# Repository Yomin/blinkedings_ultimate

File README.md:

# Blinkedings Ultimate

See http://www.netz39.de/wiki/projects:2013:blinkedings_ultimate for more information.

## License

MIT

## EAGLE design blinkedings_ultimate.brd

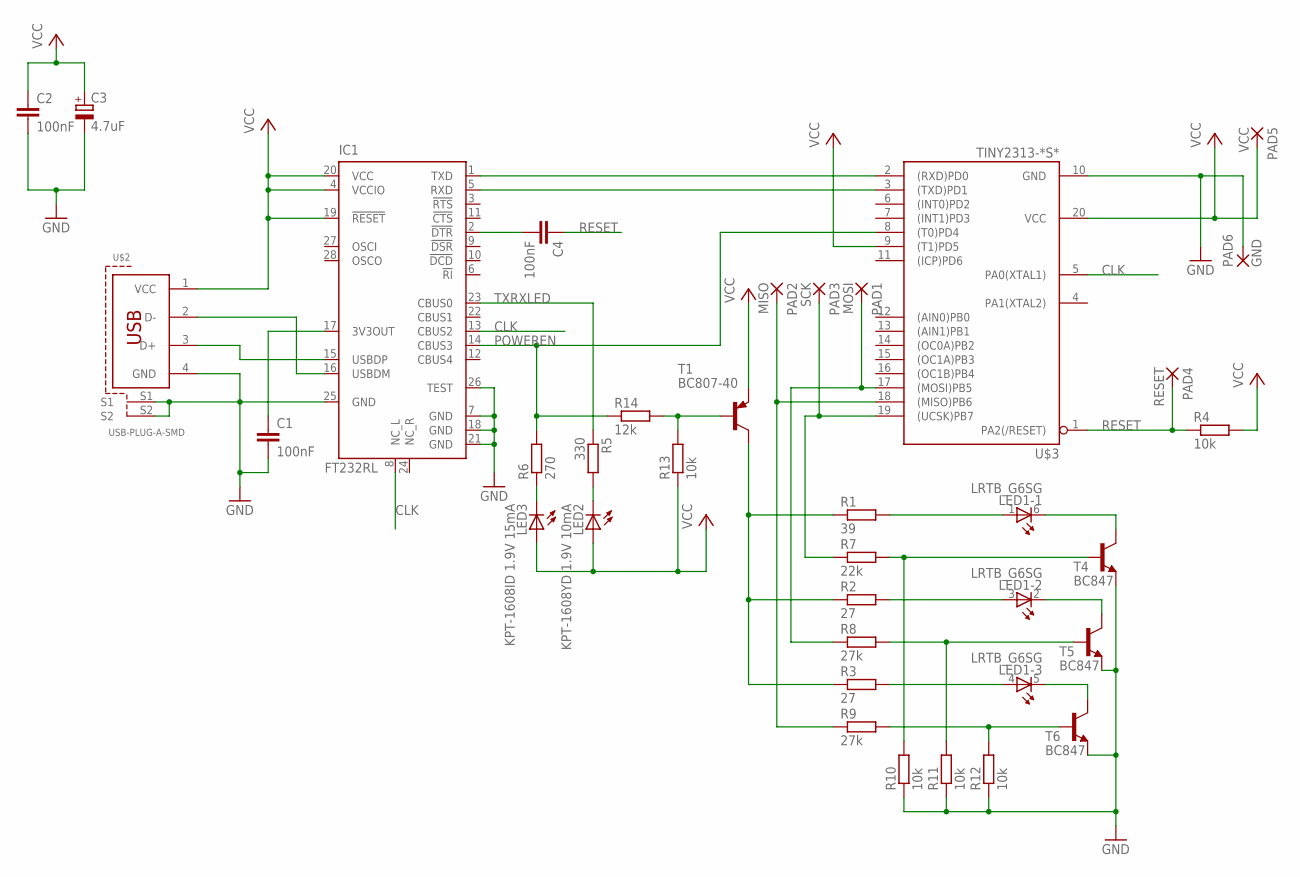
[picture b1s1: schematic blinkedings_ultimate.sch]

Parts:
C1, C2, C4: 100nF; C0603
C3: 4.7uF; SMC_C
IC1: FT232RL; SSOP28
LED1: LRTB_G6SG
LED2: KPT-1608YD 1.9V 10mA; CHIP-LED0603
LED3: KPT-1608ID 1.9V 15mA; CHIP-LED0603
PAD1: MOSI; SMD1,27-2,54
PAD2: MISO; SMD1,27-2,54
PAD3: SCK; SMD1,27-2,54
PAD4: RESET; SMD1,27-2,54
PAD5: VCC; SMD1,27-2,54
PAD6: GND; SMD1,27-2,54
R1: 39; R0603
R2, R3: 27; R0603
R4, R10, R11, R12, R13: 10k; R0603
R5: 330; R0603
R6: 270; R0603
R7: 22k; R0603
R8, R9: 27k; R0603
R14: 12k; R0603
T1: BC807-40; SOT23-BEC
T4, T5, T6: BC847; SOT23
U$2: USB-PLUG-A-SMD; USB-A-SMD
U$3: TINY2313-*S*; SO20L$

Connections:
CLK: IC1.8 (NC_L), IC1.13 (CBUS2), U$3.5 (PA0(XTAL1))
DTR: C4.2, IC1.2 (!DTR)
GND: C1.2, C2.2, C3.-, IC1.7 (GND), IC1.18 (GND), IC1.21 (GND), IC1.25 (GND), IC1.26 (TEST), PAD6.1, R10.1, R11.1, R12.1, T4.2 (E), T5.2 (E), T6.2 (E), U$2.4 (GND), U$2.S1, U$2.S2, U$3.10 (GND)
unnamed: C1.1, IC1.17 (3V3OUT)
unnamed: IC1.16 (USBDM), U$2.2 (D-)
unnamed: IC1.15 (USBDP), U$2.3 (D+)
unnamed: LED3.C, R6.1
unnamed: IC1.5 (RXD), U$3.3 ((TXD)PD1)
unnamed: IC1.1 (TXD), U$3.2 ((RXD)PD0)
unnamed: LED2.C, R5.2
unnamed: LED1.6 (C), T4.3 (C)
unnamed: LED1.3 (A), R2.2
unnamed: LED1.4 (A), R3.2
unnamed: LED1.1 (A), R1.2
unnamed: R9.2, R12.2, T6.1 (B)
unnamed: R8.2, R11.2, T5.1 (B)
unnamed: PAD2.1, R9.1, U$3.18 ((MISO)PB6)
unnamed: PAD3.1, R7.1, U$3.19 ((UCSK)PB7)
unnamed: R7.2, R10.2, T4.1 (B)
unnamed: LED1.2 (C), T5.3 (C)
unnamed: R1.1, R2.1, R3.1, T1.C
unnamed: LED1.5 (C), T6.3 (C)
unnamed: R13.2, R14.2, T1.B
unnamed: PAD1.1, R8.1, U$3.17 ((MOSI)PB5)
POWEREN: IC1.14 (CBUS3), R6.2, R14.1, U$3.8 ((T0)PD4)
RESET: C4.1, PAD4.1, R4.1, U$3.1 (PA2(/RESET))
TXRXLED: IC1.23 (CBUS0), R5.1
VCC: C2.1, C3.+, IC1.4 (VCCIO), IC1.19 (!RESET), IC1.20 (VCC), LED2.A, LED3.A, PAD5.1, R4.2, R13.1, T1.E, U$2.1 (VCC), U$3.9 ((T1)PD5), U$3.20 (VCC)

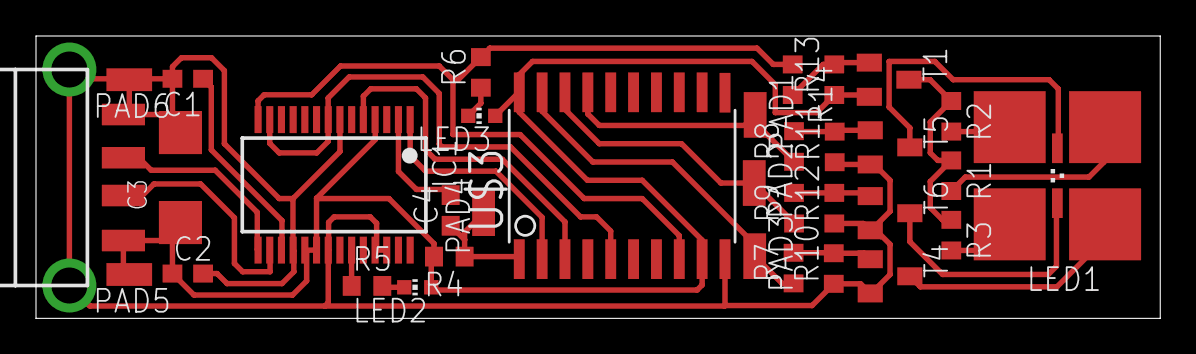
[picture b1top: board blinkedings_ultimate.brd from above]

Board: 2 copper layers, 62.5 x 15.7 mm, 34 parts (0 on the bottom side), 28 nets.

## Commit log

2013-03-25 init
2013-03-27 move led to emitter circuit, add appropriate base resitors
2013-03-27 27k base resistors for blue and green
2013-03-27 add board
2013-03-27 BC807-16 -> BC807-40
2014-01-01 fix wrong sck/miso/mosi pins
